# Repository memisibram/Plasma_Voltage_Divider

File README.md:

# Plasma_Voltage_Divider
Plasma Voltage Divider

### About the project
An electronic circuit for reading voltage from plasma machines.

Plasma machines output up to 200v. We need a voltage divider to read this voltage and use it in projects such as THC. This circuit gives output between 0 and 5v by dividing the voltage for use in controllers such as Atmega.

 - Video: [https://www.youtube.com/watch?v=IpVODe6NoKA](https://youtu.be/YBrCMQDwGMo)

### Drawing program
It was prepared using the Cross Platform and Open Source Electronics Design Automation Suite KiCad 6.0.

### Required components:
 - 2 x	5.1v - Zener Diode for D1,D2
 - 2 x	10µF/25V or 16v- Electrolytic Capacitor for C6,C7
 - 2 x	9x12 - 30mH Radial D9.5mm P5.00mm inductor for L1,L2
 - 4 x	1nF - Ceramic disc for C5,C2,C3,C4
 - 2 x	LM358 - op-amp for U1,U3
 - 1 x	100R - 1/4w or 1/2w for R5
 - 1 x	B1212S-1WR3 for BS1
 - 2 x	47k - 1/4w or 1/2w for R4,R6
 - 1 x	47nF 1KV  - High Voltage Ceramic Capacitor for C1
 - 1 x	HCNR200 - high-linearity analog optocoupler for U2
 - 1 x	3k9 - 5W - Power Resistor Ceramic Cement Resistor for R3
 - 2 x	100k - 5W - Power Resistor Ceramic Cement Resistor for R1,R2
 - 1 x	1x02_P5.00mm_Horizontal - Plasma Negative Electrode Terminal for J1
 - 1 x	1x02_P5.00mm_Horizontal - Plasma Positive Work Terminal for J3
 - 1 x	1x04_P5.00mm_Horizontal - Power / Output Terminal for J2

### Pictures

### License GNU GPL v3.0

### Donation

  -  Paypal: memisibram@gmail.com or https://www.paypal.me/memisibram

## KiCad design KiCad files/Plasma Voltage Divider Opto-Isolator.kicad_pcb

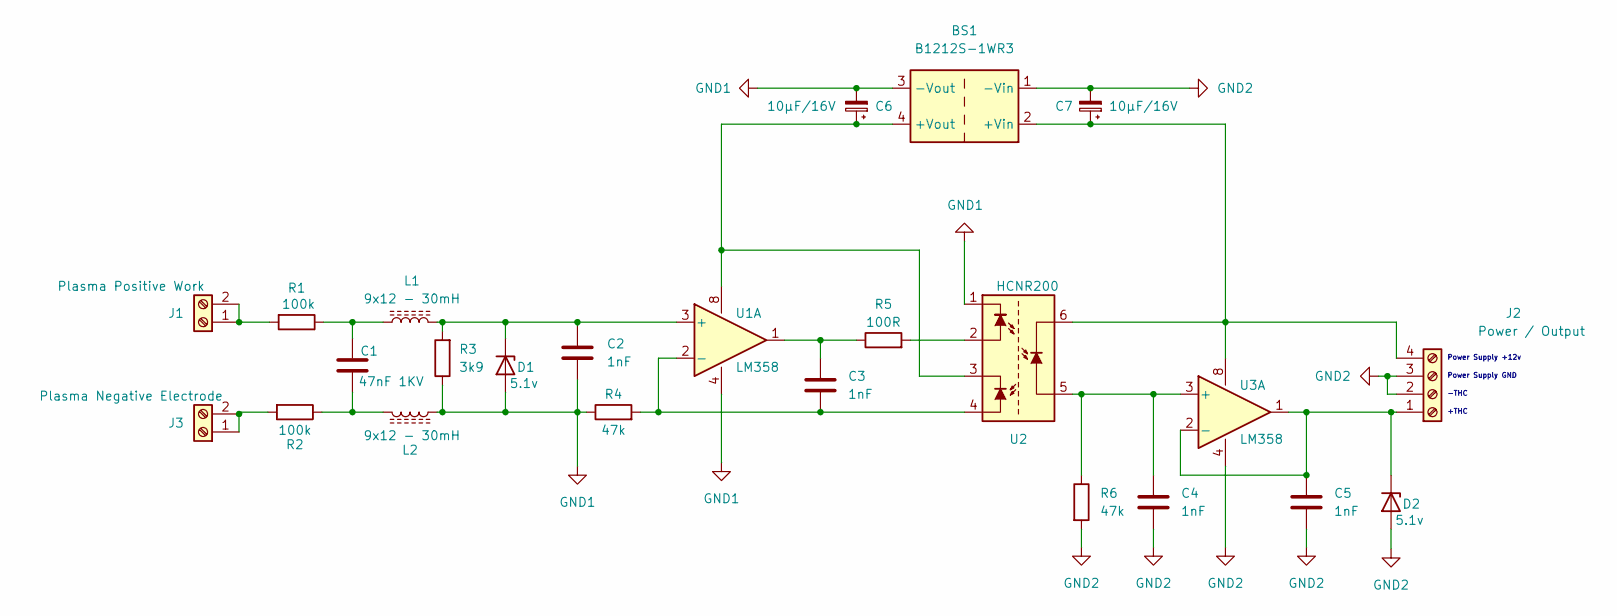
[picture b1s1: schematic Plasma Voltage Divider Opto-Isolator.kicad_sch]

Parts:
BS1: B1212S-1WR3; Converter_DCDC_Murata_MEE1SxxxxSC_THT
C1: 47nF 1KV; C_Disc_D7.5mm_W5.0mm_P7.50mm
C2, C3, C4, C5: 1nF; C_Disc_D5.0mm_W2.5mm_P5.00mm
C6, C7: 10µF/16V; CP_Radial_D8.0mm_P5.00mm
D1, D2: 5.1v; D_DO-34_SOD68_P10.16mm_Horizontal
J1: Plasma Positive Work; TerminalBlock_MetzConnect_Type094_RT03502HBLU_1x02_P5.00mm_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
J2: Power / Output; TerminalBlock_MetzConnect_Type094_RT03504HBLU_1x04_P5.00mm_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
J3: Plasma Negative Electrode; TerminalBlock_MetzConnect_Type094_RT03502HBLU_1x02_P5.00mm_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
L1, L2: 9x12 - 30mH; L_Radial_D9.5mm_P5.00mm_Fastron_07HVP
R1, R2: 100k; R_Axial_DIN0922_L20.0mm_D9.0mm_P25.40mm_Horizontal
R3: 3k9; R_Axial_DIN0922_L20.0mm_D9.0mm_P25.40mm_Horizontal
R4, R6: 47k; R_Axial_DIN0207_L6.3mm_D2.5mm_P10.16mm_Horizontal
R5: 100R; R_Axial_DIN0207_L6.3mm_D2.5mm_P10.16mm_Horizontal
U1, U3: LM358; DIP-8_W7.62mm
U2: HCNR200; DIP-8_W7.62mm

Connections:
GND1: BS1.3 (-Vout), C2.2, C6.2, D1.2 (A), L2.1, R3.1, R4.1, U1.4 (V-), U2.1
GND2: BS1.1 (-Vin), C4.2, C5.2, C7.2, D2.2 (A), J2.2, J2.3, R6.2, U3.4 (V-)
unnamed: BS1.2 (+Vin), C7.1, J2.4, U2.6, U3.8 (V+)
unnamed: BS1.4 (+Vout), C6.1, U1.8 (V+), U2.3
unnamed: C1.1, L1.1, R1.1
unnamed: C1.2, L2.2, R2.1
unnamed: C2.1, D1.1 (K), L1.2, R3.2, U1.3 (+)
unnamed: C3.1, R5.1, U1.1
unnamed: C3.2, R4.2, U1.2 (-), U2.4
unnamed: C4.1, R6.1, U2.5, U3.3 (+)
unnamed: C5.1, D2.1 (K), J2.1, U3.1, U3.2 (-)
unnamed: J1.1, J1.2, R1.2
unnamed: J3.1, J3.2, R2.2
unnamed: R5.2, U2.2

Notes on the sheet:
Power Supply GND
Power Supply +12v
-THC
+THC

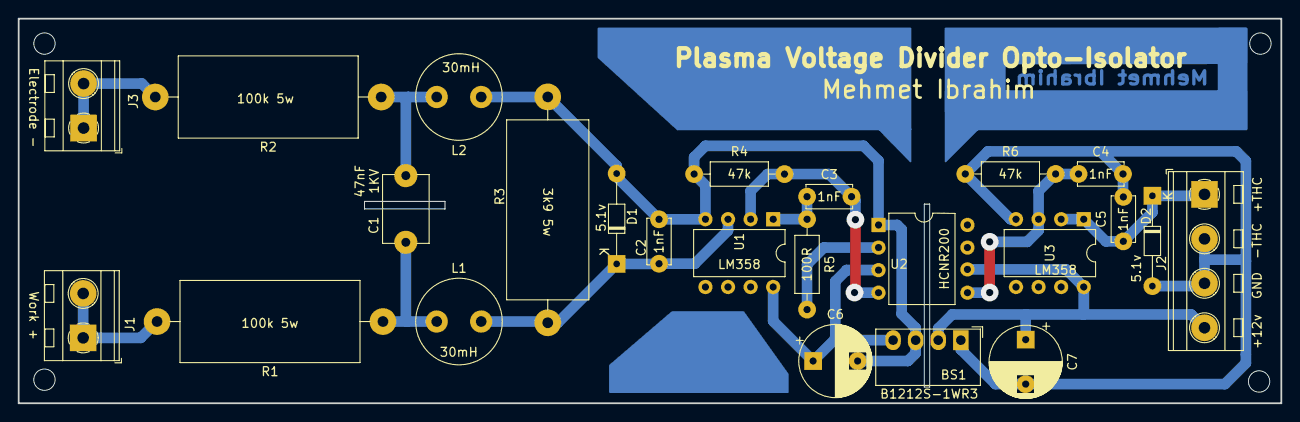
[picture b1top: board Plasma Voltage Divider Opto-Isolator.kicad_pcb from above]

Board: 2 copper layers, 142.0 x 43.2 mm, 24 parts (0 on the bottom side), 14 nets.
